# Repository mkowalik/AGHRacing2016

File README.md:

Data Logger and Telemetry device for AGH Racing Team bolid based on STM32-F4Discovery Evaluation Board.

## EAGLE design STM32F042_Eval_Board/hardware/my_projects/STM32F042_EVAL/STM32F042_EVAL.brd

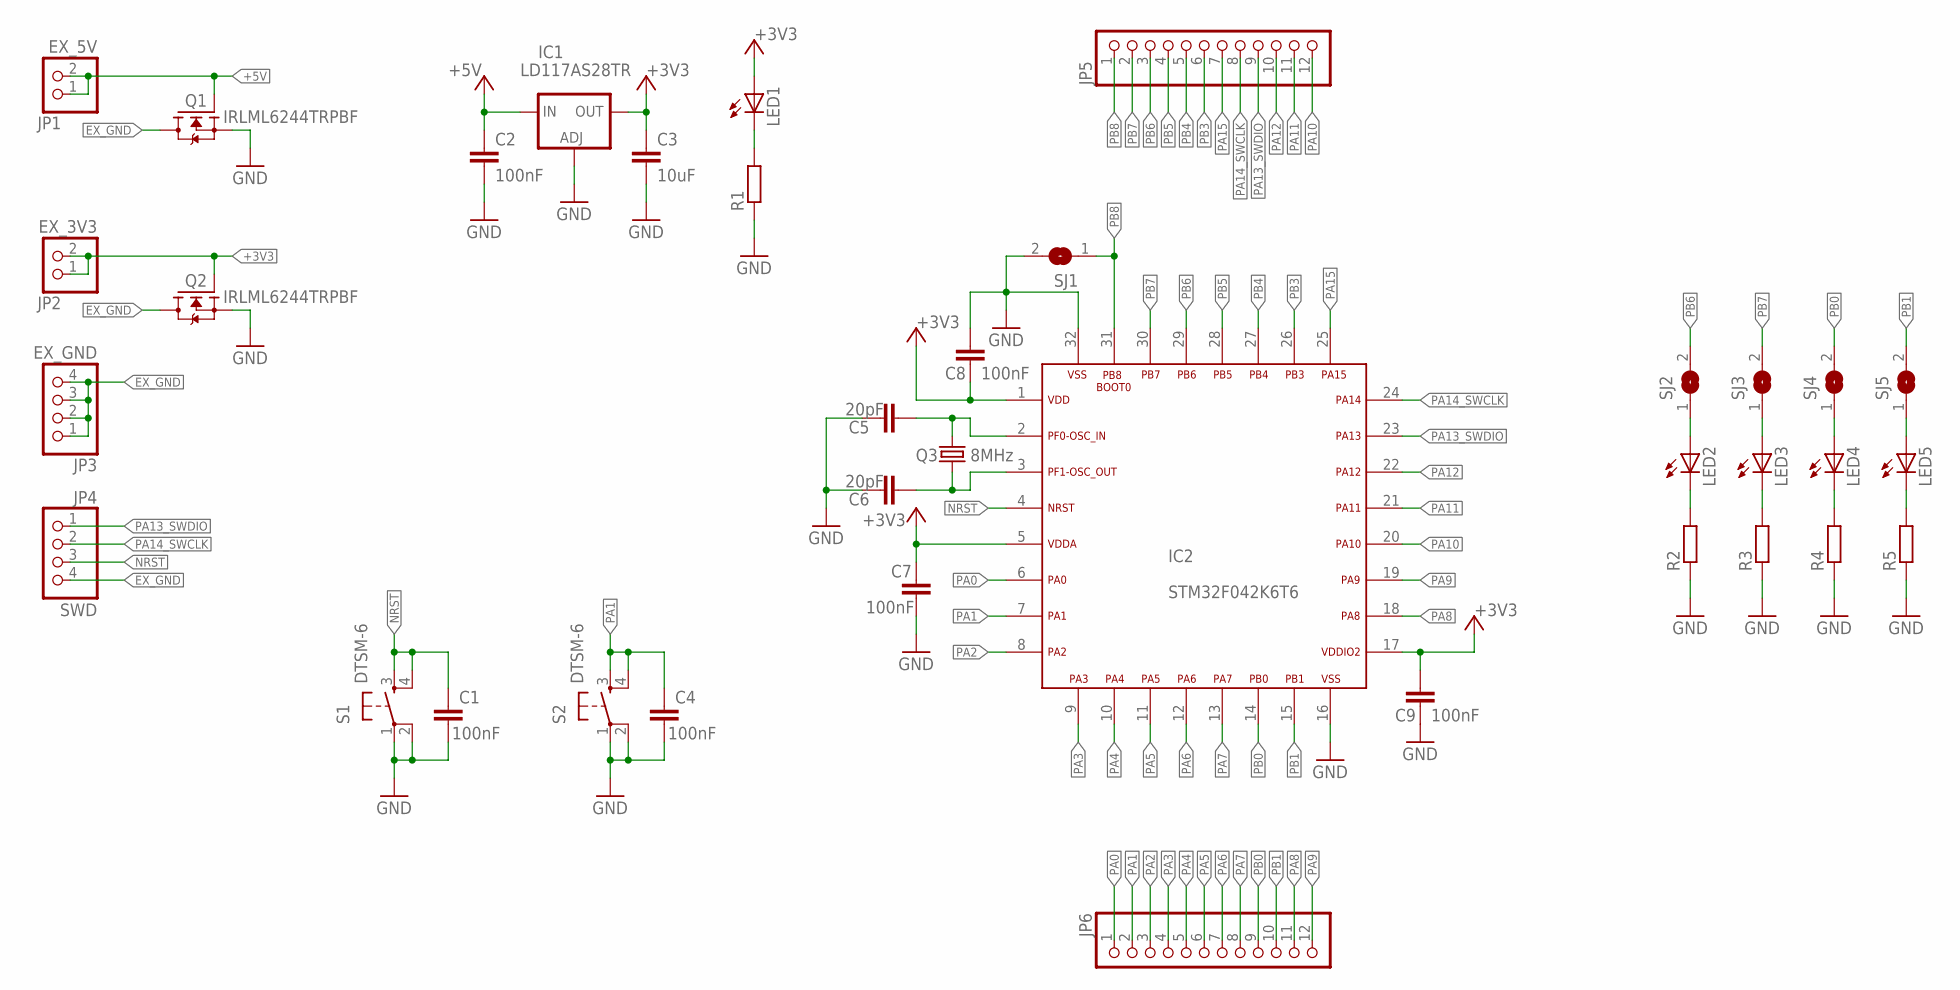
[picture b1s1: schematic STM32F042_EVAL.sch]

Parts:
C1, C2, C4, C7, C8, C9: 100nF; C0603
C3: 10uF; C0603
C5, C6: 20pF; C0603
IC1: LD117AS28TR; SOT223
IC2: STM32F042K6T6; LQFP32-7X7
JP1: EX_5V; 1X02
JP2: EX_3V3; 1X02
JP3: EX_GND; 1X04
JP4: SWD; 1X04
JP5, JP6: PINHD-1X12; 1X12
LED1, LED2, LED3, LED4, LED5: LEDCHIP-LED0603; CHIP-LED0603
Q1, Q2: IRLML6244TRPBF; SOT23
Q3: 8MHz; HC49UP
R1: R-EU_R0603; R0603
R2, R3, R4, R5: R-EU_R0805; R0805
S1, S2: DTSM-6
SJ1, SJ2, SJ3, SJ4, SJ5: SJ

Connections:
+3V3: C3.1, C7.1, C8.2, C9.1, IC1.4 (OUT), IC2.1 (VDD), IC2.5 (VDDA), IC2.17 (VDDIO2), JP2.1, JP2.2, LED1.A, Q2.1 (G)
+5V: C2.1, IC1.3 (IN), JP1.1, JP1.2, Q1.1 (G)
EX_GND: JP3.1, JP3.2, JP3.3, JP3.4, JP4.4, Q1.3 (D), Q2.3 (D)
GND: C1.2, C2.2, C3.2, C4.2, C5.1, C6.1, C7.2, C8.1, C9.2, IC1.1 (ADJ), IC2.16 (VSS1), IC2.32 (VSS2), Q1.2 (S), Q2.2 (S), R1.1, R2.1, R3.1, R4.1, R5.1, S1.1, S1.2, S2.1, S2.2, SJ1.2
unnamed: LED1.C, R1.2
unnamed: LED2.C, R2.2
unnamed: LED3.C, R3.2
unnamed: LED4.C, R4.2
unnamed: LED5.C, R5.2
unnamed: LED2.A, SJ2.1
unnamed: LED3.A, SJ3.1
unnamed: LED4.A, SJ4.1
unnamed: LED5.A, SJ5.1
unnamed: C6.2, IC2.3 (PF1-OSC_OUT), Q3.1
unnamed: C5.2, IC2.2 (PF0-OSC_IN), Q3.2
NRST: C1.1, IC2.4 (NRST), JP4.3, S1.3, S1.4
PA0: IC2.6 (PA0), JP6.1
PA1: C4.1, IC2.7 (PA1), JP6.2, S2.3, S2.4
PA2: IC2.8 (PA2), JP6.3
PA3: IC2.9 (PA3), JP6.4
PA4: IC2.10 (PA4), JP6.5
PA5: IC2.11 (PA5), JP6.6
PA6: IC2.12 (PA6), JP6.7
PA7: IC2.13 (PA7), JP6.8
PA8: IC2.18 (PA8), JP6.11
PA9: IC2.19 (PA9), JP6.12
PA10: IC2.20 (PA10), JP5.12
PA11: IC2.21 (PA11), JP5.11
PA12: IC2.22 (PA12), JP5.10
PA13_SWDIO: IC2.23 (PA13), JP4.1, JP5.9
PA14_SWCLK: IC2.24 (PA14), JP4.2, JP5.8
PA15: IC2.25 (PA15), JP5.7
PB0: IC2.14 (PB0), JP6.9, SJ4.2
PB1: IC2.15 (PB1), JP6.10, SJ5.2
PB3: IC2.26 (PB3), JP5.6
PB4: IC2.27 (PB4), JP5.5
PB5: IC2.28 (PB5), JP5.4
PB6: IC2.29 (PB6), JP5.3, SJ2.2
PB7: IC2.30 (PB7), JP5.2, SJ3.2
PB8: IC2.31 (PB8-BOOT0), JP5.1, SJ1.1

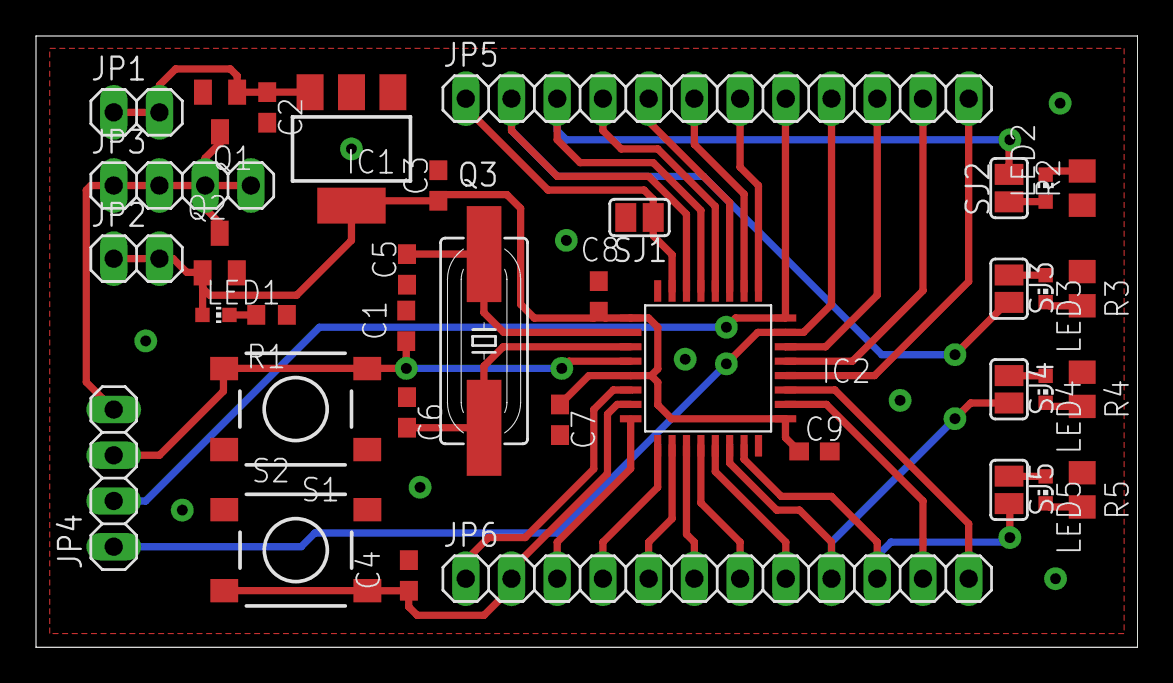
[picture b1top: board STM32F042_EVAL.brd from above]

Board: 2 copper layers, 61.2 x 34.0 mm, 37 parts (0 on the bottom side), 40 nets.

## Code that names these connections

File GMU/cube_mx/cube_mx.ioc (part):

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Mcu.Name=STM32F042K6Tx
Mcu.Package=LQFP32
Mcu.UserName=STM32F042K6Tx
PA10.GPIOParameters=GPIO_Speed,GPIO_PuPd,GPIO_Label
PA10.GPIO_Label=GEAR_UP_TIM
PA10.GPIO_PuPd=GPIO_PULLUP
PA10.GPIO_Speed=GPIO_SPEED_FREQ_HIGH
PA10.Signal=S_TIM1_CH3
PA11.Mode=Master
PA11.Signal=CAN_RX
PA12.Mode=Master
PA12.Signal=CAN_TX
PA13.Mode=Serial_Wire
PA13.Signal=SYS_SWDIO
PA14.Mode=Serial_Wire
PA14.Signal=SYS_SWCLK
PA15.Signal=S_TIM2_CH1_ETR
PA2.Mode=Asynchronous
PA2.Signal=USART2_TX
PA3.Mode=Asynchronous
PA3.Signal=USART2_RX
PA5.GPIOParameters=GPIO_Speed,GPIO_PuPd,GPIO_Label
PA5.GPIO_Label=CLUTCH_OUT
PA5.GPIO_PuPd=GPIO_PULLDOWN
PA5.GPIO_Speed=GPIO_SPEED_FREQ_HIGH
PA5.Signal=GPIO_Output
PA6.GPIOParameters=GPIO_Speed,GPIO_PuPd,GPIO_Label
PA6.GPIO_Label=GEAR_DOWN_OUT
PA6.GPIO_PuPd=GPIO_PULLDOWN
PA6.GPIO_Speed=GPIO_SPEED_FREQ_HIGH
PA6.Signal=GPIO_Output
PA7.GPIOParameters=GPIO_Speed,GPIO_PuPd,GPIO_Label
PA7.GPIO_Label=GEAR_UP_OUT
PA7.GPIO_PuPd=GPIO_PULLDOWN
PA7.GPIO_Speed=GPIO_SPEED_FREQ_HIGH
PA7.Signal=GPIO_Output
PA8.GPIOParameters=GPIO_Speed,GPIO_PuPd,GPIO_Label
PA8.GPIO_Label=CLUTCH_TIM
PA8.GPIO_PuPd=GPIO_PULLUP
PA8.GPIO_Speed=GPIO_SPEED_FREQ_HIGH
PA8.Signal=S_TIM1_CH1
PA9.GPIOParameters=GPIO_Speed,GPIO_PuPd,GPIO_Label
PA9.GPIO_Label=GEAR_DOWN_TIM
PA9.GPIO_PuPd=GPIO_PULLUP
PA9.GPIO_Speed=GPIO_SPEED_FREQ_HIGH
PA9.Signal=S_TIM1_CH2
PB0.Mode=IN8
PB0.Signal=ADC_IN8
PB1.Mode=IN9
PB1.Signal=ADC_IN9
PB4.GPIOParameters=GPIO_PuPd,GPIO_Label
PB4.GPIO_Label=NEUTRAL_IN
PB4.GPIO_PuPd=GPIO_PULLUP
PB4.Signal=GPIO_Input
PB5.GPIOParameters=GPIO_Speed,GPIO_PuPd,GPIO_Label
PB5.GPIO_Label=GEAR_CUT
PB5.GPIO_PuPd=GPIO_PULLDOWN
PB5.GPIO_Speed=GPIO_SPEED_FREQ_HIGH
PB5.Signal=GPIO_Output
PF0-OSC_IN.Mode=HSE-External-Oscillator
PF0-OSC_IN.Signal=RCC_OSC_IN
PF1-OSC_OUT.Mode=HSE-External-Oscillator
PF1-OSC_OUT.Signal=RCC_OSC_OUT
RCC.SYSCLKFreq_VALUE=48000000
RCC.SYSCLKSource=RCC_SYSCLKSOURCE_PLLCLK
board=cube_mx

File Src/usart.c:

/**
  ******************************************************************************
  * File Name          : USART.c
  * Description        : This file provides code for the configuration
  *                      of the USART instances.
  ******************************************************************************
  *
  * COPYRIGHT(c) 2016 STMicroelectronics
  *
  * Redistribution and use in source and binary forms, with or without modification,
  * are permitted provided that the following conditions are met:
  *   1. Redistributions of source code must retain the above copyright notice,
  *      this list of conditions and the following disclaimer.
  *   2. Redistributions in binary form must reproduce the above copyright notice,
  *      this list of conditions and the following disclaimer in the documentation
  *      and/or other materials provided with the distribution.
  *   3. Neither the name of STMicroelectronics nor the names of its contributors
  *      may be used to endorse or promote products derived from this software
  *      without specific prior written permission.
  *
  * THIS SOFTWARE IS PROVIDED BY THE COPYRIGHT HOLDERS AND CONTRIBUTORS "AS IS"
  * AND ANY EXPRESS OR IMPLIED WARRANTIES, INCLUDING, BUT NOT LIMITED TO, THE
  * IMPLIED WARRANTIES OF MERCHANTABILITY AND FITNESS FOR A PARTICULAR PURPOSE ARE
  * DISCLAIMED. IN NO EVENT SHALL THE COPYRIGHT HOLDER OR CONTRIBUTORS BE LIABLE
  * FOR ANY DIRECT, INDIRECT, INCIDENTAL, SPECIAL, EXEMPLARY, OR CONSEQUENTIAL
  * DAMAGES (INCLUDING, BUT NOT LIMITED TO, PROCUREMENT OF SUBSTITUTE GOODS OR
  * SERVICES; LOSS OF USE, DATA, OR PROFITS; OR BUSINESS INTERRUPTION) HOWEVER
  * CAUSED AND ON ANY THEORY OF LIABILITY, WHETHER IN CONTRACT, STRICT LIABILITY,
  * OR TORT (INCLUDING NEGLIGENCE OR OTHERWISE) ARISING IN ANY WAY OUT OF THE USE
  * OF THIS SOFTWARE, EVEN IF ADVISED OF THE POSSIBILITY OF SUCH DAMAGE.
  *
  ******************************************************************************
  */

/* Includes ------------------------------------------------------------------*/
#include "usart.h"

#include "gpio.h"
#include "dma.h"

/* USER CODE BEGIN 0 */

#include "ecumaster.h"

/* USER CODE END 0 */

UART_HandleTypeDef huart1;
UART_HandleTypeDef huart2;
DMA_HandleTypeDef hdma_usart1_rx;
DMA_HandleTypeDef hdma_usart2_tx;

/* USART1 init function */

void MX_USART1_UART_Init(void)
{

  huart1.Instance = USART1;
  huart1.Init.BaudRate = 19200;
  huart1.Init.WordLength = UART_WORDLENGTH_8B;
  huart1.Init.StopBits = UART_STOPBITS_1;
  huart1.Init.Parity = UART_PARITY_NONE;
  huart1.Init.Mode = UART_MODE_RX;
  huart1.Init.HwFlowCtl = UART_HWCONTROL_NONE;
  huart1.Init.OverSampling = UART_OVERSAMPLING_16;
  HAL_UART_Init(&huart1);

}
/* USART2 init function */

void MX_USART2_UART_Init(void)
{

  huart2.Instance = USART2;
  huart2.Init.BaudRate = 9600;
  huart2.Init.WordLength = UART_WORDLENGTH_8B;
  huart2.Init.StopBits = UART_STOPBITS_1;
  huart2.Init.Parity = UART_PARITY_NONE;
  huart2.Init.Mode = UART_MODE_TX;
  huart2.Init.HwFlowCtl = UART_HWCONTROL_NONE;
  huart2.Init.OverSampling = UART_OVERSAMPLING_16;
  HAL_UART_Init(&huart2);

}

void HAL_UART_MspInit(UART_HandleTypeDef* huart)
{

  GPIO_InitTypeDef GPIO_InitStruct;
  if(huart->Instance==USART1)
  {
  /* USER CODE BEGIN USART1_MspInit 0 */

  /* USER CODE END USART1_MspInit 0 */
    /* Peripheral clock enable */
    __USART1_CLK_ENABLE();
  
    /**USART1 GPIO Configuration    
    PB6     ------> USART1_TX
    PB7     ------> USART1_RX 
    */
    GPIO_InitStruct.Pin = GPIO_PIN_6|GPIO_PIN_7;
    GPIO_InitStruct.Mode = GPIO_MODE_AF_PP;
    GPIO_InitStruct.Pull = GPIO_PULLUP;
    GPIO_InitStruct.Speed = GPIO_SPEED_HIGH;
    GPIO_InitStruct.Alternate = GPIO_AF7_USART1;
    HAL_GPIO_Init(GPIOB, &GPIO_InitStruct);

    /* Peripheral DMA init*/
  
    hdma_usart1_rx.Instance = DMA2_Stream2;
    hdma_usart1_rx.Init.Channel = DMA_CHANNEL_4;
    hdma_usart1_rx.Init.Direction = DMA_PERIPH_TO_MEMORY;
    hdma_usart1_rx.Init.PeriphInc = DMA_PINC_DISABLE;
    hdma_usart1_rx.Init.MemInc = DMA_MINC_ENABLE;
    hdma_usart1_rx.Init.PeriphDataAlignment = DMA_PDATAALIGN_BYTE;
    hdma_usart1_rx.Init.MemDataAlignment = DMA_MDATAALIGN_BYTE;
    hdma_usart1_rx.Init.Mode = DMA_CIRCULAR;
    hdma_usart1_rx.Init.Priority = DMA_PRIORITY_HIGH;
    hdma_usart1_rx.Init.FIFOMode = DMA_FIFOMODE_DISABLE;
    HAL_DMA_Init(&hdma_usart1_rx);

    __HAL_LINKDMA(huart,hdmarx,hdma_usart1_rx);

    /* Peripheral interrupt init*/
    HAL_NVIC_SetPriority(USART1_IRQn, 5, 0);
    HAL_NVIC_EnableIRQ(USART1_IRQn);
  /* USER CODE BEGIN USART1_MspInit 1 */

  /* USER CODE END USART1_MspInit 1 */
  }
  else if(huart->Instance==USART2)
  {
  /* USER CODE BEGIN USART2_MspInit 0 */

  /* USER CODE END USART2_MspInit 0 */
    /* Peripheral clock enable */
    __USART2_CLK_ENABLE();
  
    /**USART2 GPIO Configuration    
    PA2     ------> USART2_TX
    PA3     ------> USART2_RX 
    */
    GPIO_InitStruct.Pin = GPIO_PIN_2|GPIO_PIN_3;
    GPIO_InitStruct.Mode = GPIO_MODE_AF_PP;
    GPIO_InitStruct.Pull = GPIO_PULLUP;
    GPIO_InitStruct.Speed = GPIO_SPEED_HIGH;
    GPIO_InitStruct.Alternate = GPIO_AF7_USART2;
    HAL_GPIO_Init(GPIOA, &GPIO_InitStruct);

    /* Peripheral DMA init*/
  
    hdma_usart2_tx.Instance = DMA1_Stream6;
    hdma_usart2_tx.Init.Channel = DMA_CHANNEL_4;
    hdma_usart2_tx.Init.Direction = DMA_MEMORY_TO_PERIPH;
    hdma_usart2_tx.Init.PeriphInc = DMA_PINC_DISABLE;
    hdma_usart2_tx.Init.MemInc = DMA_MINC_ENABLE;
    hdma_usart2_tx.Init.PeriphDataAlignment = DMA_PDATAALIGN_BYTE;
    hdma_usart2_tx.Init.MemDataAlignment = DMA_MDATAALIGN_BYTE;
    hdma_usart2_tx.Init.Mode = DMA_NORMAL;
    hdma_usart2_tx.Init.Priority = DMA_PRIORITY_MEDIUM;
    hdma_usart2_tx.Init.FIFOMode = DMA_FIFOMODE_DISABLE;
    HAL_DMA_Init(&hdma_usart2_tx);

    __HAL_LINKDMA(huart,hdmatx,hdma_usart2_tx);

    /* Peripheral interrupt init*/
    HAL_NVIC_SetPriority(USART2_IRQn, 5, 0);
    HAL_NVIC_EnableIRQ(USART2_IRQn);
  /* USER CODE BEGIN USART2_MspInit 1 */

  /* USER CODE END USART2_MspInit 1 */
  }
}

void HAL_UART_MspDeInit(UART_HandleTypeDef* huart)
{

  if(huart->Instance==USART1)
  {
  /* USER CODE BEGIN USART1_MspDeInit 0 */

  /* USER CODE END USART1_MspDeInit 0 */
    /* Peripheral clock disable */
    __USART1_CLK_DISABLE();
  
    /**USART1 GPIO Configuration    
    PB6     ------> USART1_TX
    PB7     ------> USART1_RX 
    */
    HAL_GPIO_DeInit(GPIOB, GPIO_PIN_6|GPIO_PIN_7);

    /* Peripheral DMA DeInit*/
    HAL_DMA_DeInit(huart->hdmarx);

    /* Peripheral interrupt Deinit*/
    HAL_NVIC_DisableIRQ(USART1_IRQn);

  /* USER CODE BEGIN USART1_MspDeInit 1 */

  /* USER CODE END USART1_MspDeInit 1 */
  }
  else if(huart->Instance==USART2)
  {
  /* USER CODE BEGIN USART2_MspDeInit 0 */

  /* USER CODE END USART2_MspDeInit 0 */
    /* Peripheral clock disable */
    __USART2_CLK_DISABLE();
  
    /**USART2 GPIO Configuration    
    PA2     ------> USART2_TX
    PA3     ------> USART2_RX 
    */
    HAL_GPIO_DeInit(GPIOA, GPIO_PIN_2|GPIO_PIN_3);

    /* Peripheral DMA DeInit*/
    HAL_DMA_DeInit(huart->hdmatx);

    /* Peripheral interrupt Deinit*/
    HAL_NVIC_DisableIRQ(USART2_IRQn);

  /* USER CODE BEGIN USART2_MspDeInit 1 */

  /* USER CODE END USART2_MspDeInit 1 */
  }
} 

/* USER CODE BEGIN 1 */

void UART2_TransmitData(volatile uint8_t* data, uint16_t size){
	  HAL_UART_StateTypeDef state = huart2.gState;
	  while ((state != HAL_UART_STATE_READY) && (state != HAL_UART_STATE_BUSY_RX)){
		  state = huart2.gState;
	  } //TODO jakos zrobic zeby bylo non-blocking
	  volatile HAL_StatusTypeDef status = HAL_UART_Transmit_DMA(&huart2, (uint8_t*)data, size);
	  if (status!=HAL_OK){
		  while(1){
			  HAL_GPIO_TogglePin(LD3_GPIO_Port, LD3_Pin);
			  HAL_Delay(100);
		  }
	  }
}

void UART1_ReceiveDataFromECU_DMA(volatile uint8_t* ecuData){
	  HAL_UART_StateTypeDef state = huart1.gState;
	  while ((state != HAL_UART_STATE_READY) && (state != HAL_UART_STATE_BUSY_TX)){
		  state = huart1.gState;
	  }	//TODO jakos zrobic zeby bylo non-blocking

	    /* Enable the UART Data Register not empty Interrupt */
	  HAL_StatusTypeDef status = HAL_UART_Receive_DMA(&huart1, ecuData, ECU_BUFFER_SIZE);
	  __HAL_UART_ENABLE_IT(&huart1, UART_IT_RXNE);
	  if (status!=HAL_OK){
		  while(1){
			  HAL_GPIO_TogglePin(LD3_GPIO_Port, LD3_Pin);
			  HAL_Delay(100);
		  }
	  }
}

/* USER CODE END 1 */

/**
  * @}
  */

/**
  * @}
  */

/************************ (C) COPYRIGHT STMicroelectronics *****END OF FILE****/

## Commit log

2015-12-09 Parsing information from ECUMASTER. Receiving it by UART using DMA, after DMA interrupt handled, starting waiting for next data from ECU (checkout: receivedDataFromECUInterruptHandler and HAL_UART_Ms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
2015-12-09 Added README.md file.
2015-12-09 In main function reimplemented prototype for testing: receiving 5 bytes - one frame of data from ECU and sending it back to UART2 (to PC for testing). Needed to implement handling interrupt DMATransf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
2015-12-15 Bug fixing. Added UART1 RX not empty interrupt enable, so when every byte of data receives from ECU, USART1_IRQHandler function in stm32xx?it.c file is called, where received bytes iterator is increm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
2016-01-03 Changed function naimg in ecumaster.h. Bug fixing after tests in garage.
2016-01-03 Added FreeRTOS tasks for ECU data management using CMSIS wrapper.
2016-01-06 Added CAN library for CAN1. Bug fixing for ECUMaster communication.
2016-01-12 Added initialisation for data interpretation table. Added parser for Ecumaster log XML file written in python. Added dashbpard files.
2016-02-11 Updated version of Cube to 4.11. Set up 1-pin SDBus for handling SD Card communication using STM32Cube software.
2016-02-11 Data Snaphot Maker class-like file provided.
2016-02-11 Implementation of SD Card saver. Not finished
2016-02-26 Simple file saving to SDCard works. Project compiles.
2016-03-03 STM32F042 Evaluation Board - Eagle project
2016-03-04 Implementation for saving sensors data on SD Card.
2016-03-04 Added mutex for actual data in every place used by application. CAN test code. Error logger placeholder. Thread for saving data to SDCard based on state machine.
2016-03-05 SD Card bug fixing. Still returns errors.
2016-03-05 Bug fixing. SD Card recording works.
2016-03-23 Added library for SH1106 OLED Display.
2016-03-29 OLED display is working fine. Button for changing display functions added. Problem with generating informations for SW by CUBE MX.
2016-04-24 Added 7-segment display implementation. Problem with still pushed Dash_Button.
2016-05-10 Bug fixing with receiving data from ECU. Still problem when ECU turned on before Logger.
2016-05-10 Updated GPIO - prepared for multiplexer for WS2812 LEDs. Still bothering with UART1 DMA problem when ECU starts first.
2016-08-03 Segment display off. Added refreshing WS2812 LEDs for noise prevention.
2016-08-05 Added CAN Sensors support. Needed documentation and tests. Needed implementation of virtual gear sensopr based on ratio of VSS and RPM.
2016-08-05 Added Gearbox Menagement Unit (GMU) code implemented by Marek Kuklis.
2016-08-18 EAGLE Lib update
2016-09-24 FS Spain checkpoint.
2016-10-13 Reorganisation and cleanup of functions, methods and files.
2016-10-29 Code refactoring.
2016-10-29 Code comments.
2019-01-10 Create LICENSE
